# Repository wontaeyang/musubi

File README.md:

# Musubi - Super thin 38 key split keyboard

Musubi is a 38 key split keyboard using Kailh X switches and Seeeduino Xiao.
This keyboard started with dust keyboard as a base and adjusted with customized layout
and design elements from my favorite keyboards.

* [dust by Hazel](https://github.com/jasonhazel/dust)
* [TOTEM by GEIST](https://github.com/GEIGEIGEIST/TOTEM)
* [Dilemma by BastardKB](https://github.com/Bastardkb/Dilemma)

#### Currently there are two versions of the keyboard

* **V1** (white)
    - a lot more index and pinky column stagger
    - Totem like thumb cluster
* **V2** (red)
    - less aggressive column staggers
    - thumb cluster is extended out
    - TRRS socket location moved
    - double puck mount for wider design

# Features

* Reversible PCB
* Column stagger with splay
* 3x5 layout with 4 additional keys (three thumb, 1 pinky)
* Slim build ( measured from keycap to bottom )
    - without case 6.7 mm
    - with case 9.7 mm
* Tenting puck support

# BOM

**Base keyboard**:
* Seeeduino Xiao RP2040 (2)
* Musubi PCB (2)
* Kailh X switches (38)
* Kailh X switch keycaps (38)
* Diodes - 1N4148W  (38)
* TRRS Jack - PJ 320A 3.5mm (2)
* TRRS cable (1)

**Optional parts**:
* Musubi case (2, optional)
    - M2 4mm screw (8)
    - M2 nuts - 4mm wide, 1.6mm tall (8)
    - Tenting pucks (2, optional)
    - Manfrotto Pocket Tripod (2, optional)
    - Rubber feet (optional without tenting pucks)

# Keyboard design files

V1 files
* [V1 PCB](https://github.com/wontaeyang/musubi/blob/main/PCB/Exports/V1/musubi-pcb.zip)
* [V1 case](https://github.com/wontaeyang/musubi/tree/main/case/V1)

V2 files
* [V2 PCB](https://github.com/wontaeyang/musubi/blob/main/PCB/Exports/V2/musubi_pcb_rev2.zip)
* [V2 case](https://github.com/wontaeyang/musubi/tree/main/case/V2)

# Firmware

Musubi's firmware is a modified copy of [Dilemma's VIA keymap](https://github.com/qmk/qmk_firmware/tree/master/keyboards/bastardkb/dilemma/3x5_2/keymaps/via).
If you want to just flash the keyboard with default keymap, put the Xiaos in to bootloader mode and copy the included UF2 file

```
// For Macs
cp -X ./firmware/musubi_default.uf2 /Volumes/RPI-RP2
```

For those who wish to customize, clone this repo and symlink Musubi firmware to QMK Firmware

```
ln -s ./firmware/musubi /{your_qmk_firmware_base_location}/qmk_firmware/keyboards/musubi
```

Adjust the layout and compile/copy the UF2 file into Xiao

```
qmk compile -kb musubi -km default
cp -X ./firmware/musubi_default.uf2 /Volumes/RPI-RP2
```

# License
This work is licensed under a [Creative Commons Attribution 4.0 International License][cc-by].

[cc-by]: http://creativecommons.org/licenses/by/4.0/

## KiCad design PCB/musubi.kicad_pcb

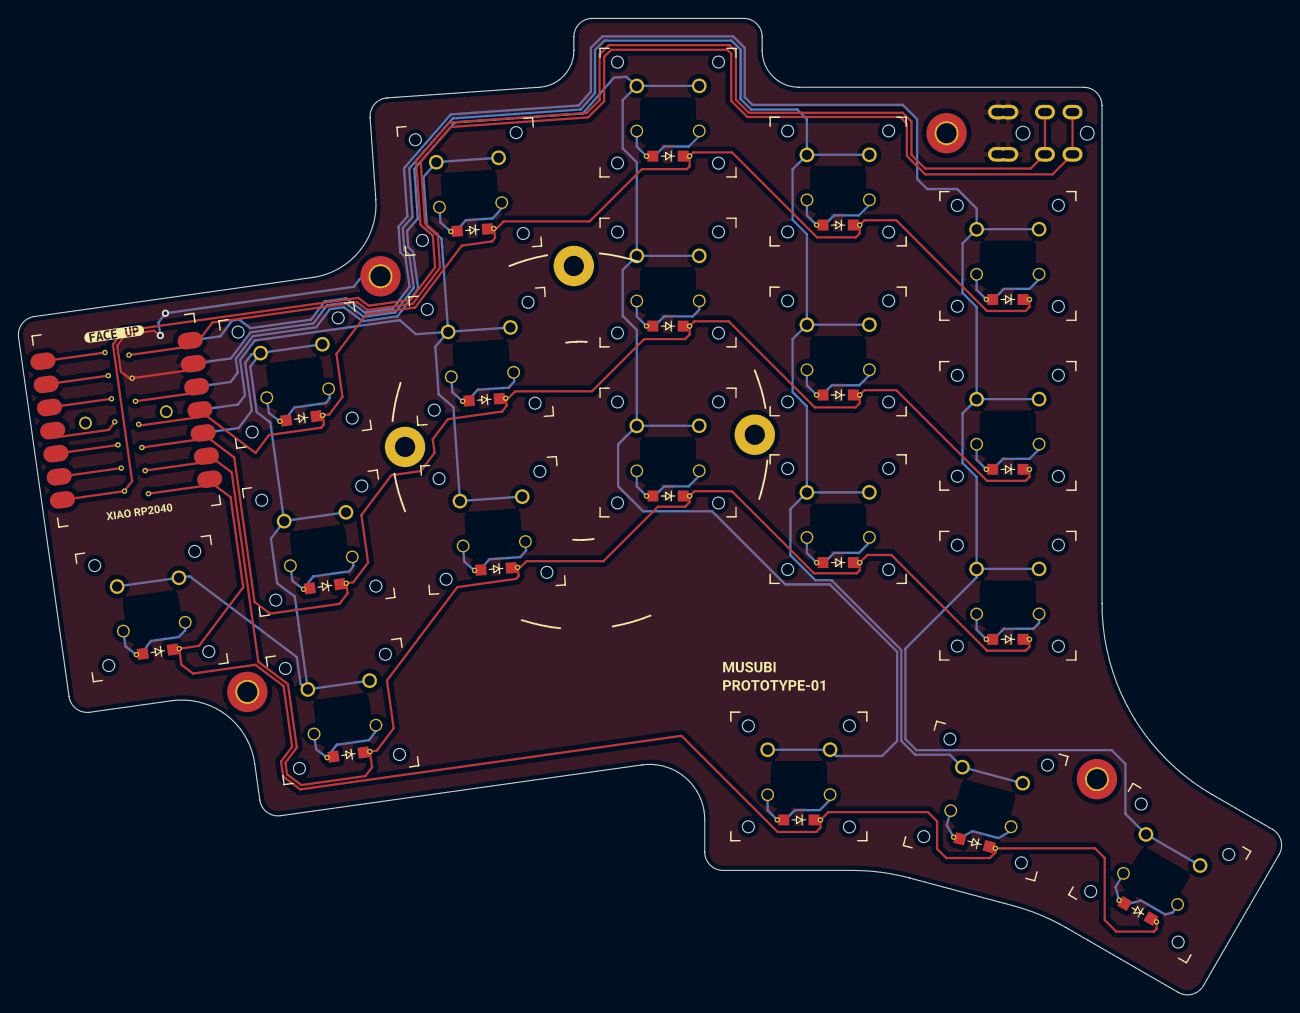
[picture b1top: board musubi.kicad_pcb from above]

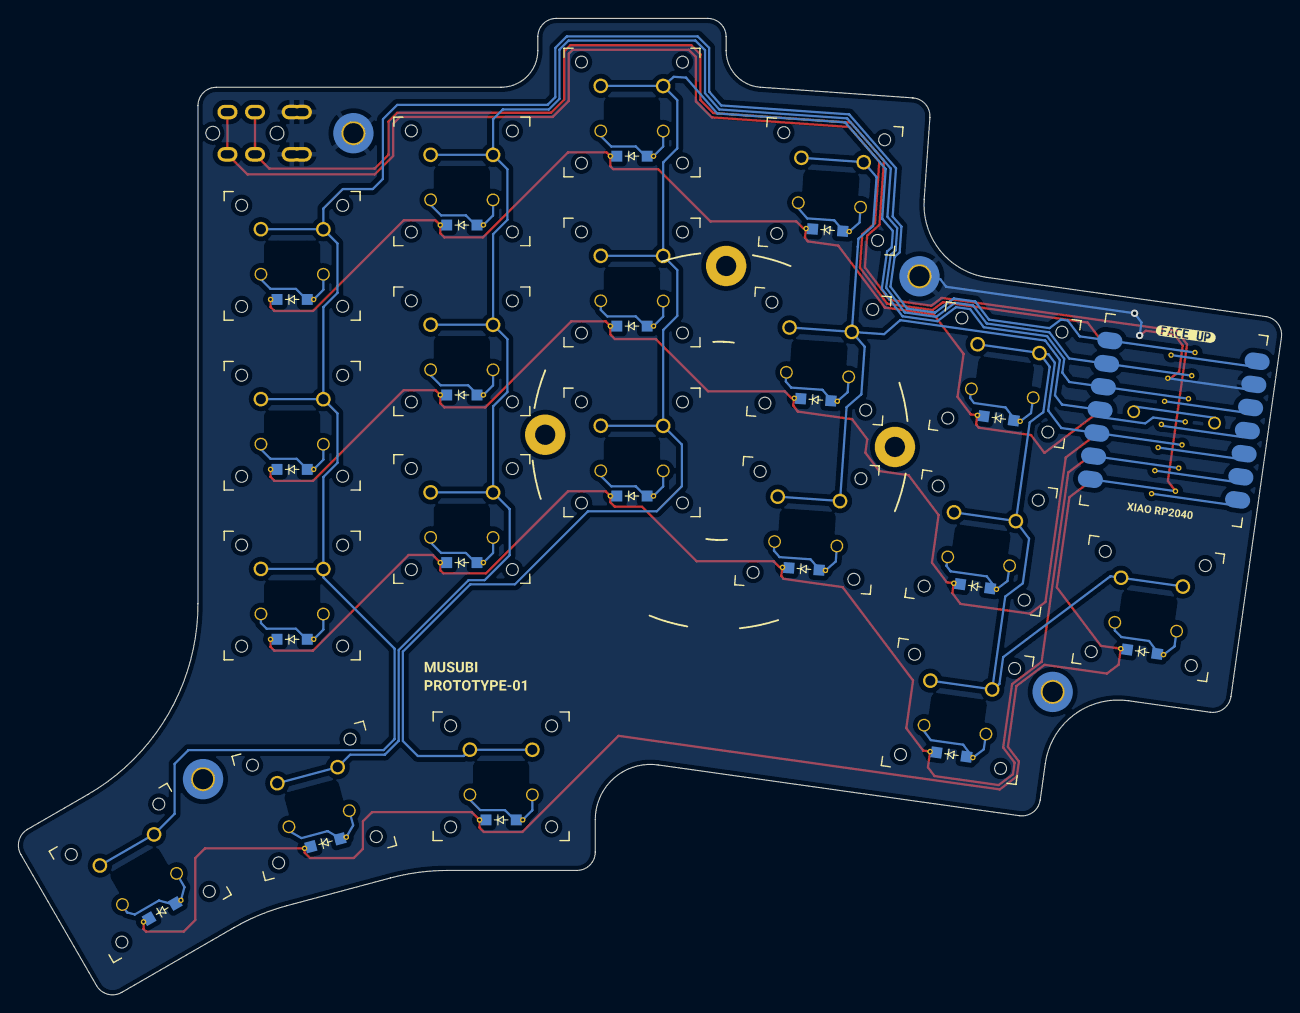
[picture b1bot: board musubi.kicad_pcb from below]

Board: 2 copper layers, 137.5 x 106.3 mm, 44 parts (2 on the bottom side), 31 nets.

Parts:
D1, D2, D3, D4, D5, D6, D7, D8, D9, D10, D11, D12, D13, D14, D15, D17, D18, D19, D20: D_Small; diode-reversible
J1: AudioJack4; TRRS-PJ-320A-dual
SW1, SW2, SW3, SW4, SW5, SW6, SW7, SW8, SW9, SW10, SW11, SW12, SW13, SW14, SW15, SW17, SW18, SW19, SW20: SW_Push_45deg; Kailh-PG1425-X-Switch-revers
U1: xiao-ble; xiao-rev-reversible
kibuzzard-63ADF2C0, kibuzzard-63ADF2C0#2: G***; kibuzzard-63ADF2C0
kibuzzard-63ADF196, kibuzzard-63ADF196#2: G***; kibuzzard-63ADF196

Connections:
COL0: SW1.1, SW6.1, SW11.1, SW17.1, U1.5 (A8_SDA/0.04_H)
COL1: SW2.1, SW7.1, SW12.1, U1.4 (A11/0.29)
COL2: SW3.1, SW8.1, SW13.1, SW18.1, U1.3 (A10/0.28)
COL3: SW4.1, SW9.1, SW14.1, SW19.1, U1.2 (A4/0.03_H)
COL4: SW5.1, SW10.1, SW15.1, SW20.1, U1.1 (A2/0.02_H)
GND: J1.1, J1.2, U1.13 (GND)
unnamed: D1.2 (A), SW1.2
unnamed: D2.2 (A), SW2.2
unnamed: D3.2 (A), SW3.2
unnamed: D4.2 (A), SW4.2
unnamed: D5.2 (A), SW5.2
unnamed: D6.2 (A), SW6.2
unnamed: D7.2 (A), SW7.2
unnamed: D8.2 (A), SW8.2
unnamed: D9.2 (A), SW9.2
unnamed: D10.2 (A), SW10.2
unnamed: D11.2 (A), SW11.2
unnamed: D12.2 (A), SW12.2
unnamed: D13.2 (A), SW13.2
unnamed: D14.2 (A), SW14.2
unnamed: D15.2 (A), SW15.2
unnamed: D17.2 (A), SW17.2
unnamed: D18.2 (A), SW18.2
unnamed: D19.2 (A), SW19.2
unnamed: D20.2 (A), SW20.2
ROW0: D1.1 (K), D2.1 (K), D3.1 (K), D4.1 (K), D5.1 (K), U1.11 (A6_MOSI/1.15)
ROW1: D6.1 (K), D7.1 (K), D8.1 (K), D9.1 (K), D10.1 (K), U1.10 (A5_MISO/1.14)
ROW2: D11.1 (K), D12.1 (K), D13.1 (K), D14.1 (K), D15.1 (K), U1.9 (A7_SCK/1.13)
ROW3: D17.1 (K), D18.1 (K), D19.1 (K), D20.1 (K), U1.8 (B9_RX/1.12)
TX: J1.3, U1.7 (B8_TX/1.11)
VCC: J1.4, U1.14 (5V)

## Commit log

2023-01-07 Adjust image
2023-01-07 Add BOM
2023-01-07 Remove random files
2023-01-07 Remove ds_stores
2023-01-08 Add firmware
2023-01-08 Update readme and add instructions
2023-01-13 Up the tap term
2023-01-14 Add reverse thumb layout
2023-01-16 Lots of stuff
2023-01-16 Try fixing image size
2023-01-16 Add more version details
2023-01-16 Rename pcb exports
2023-01-16 Add design files to readme
2023-01-16 Fix typo
2023-01-16 Rename uf2 files
2023-01-17 Add disclaimer for v2 files
2023-01-18 Reorganize cases
2023-01-18 Remove extra file
2023-01-18 Fix cases
2023-01-23 Remove v2 warning, it is now confirmed to be working
